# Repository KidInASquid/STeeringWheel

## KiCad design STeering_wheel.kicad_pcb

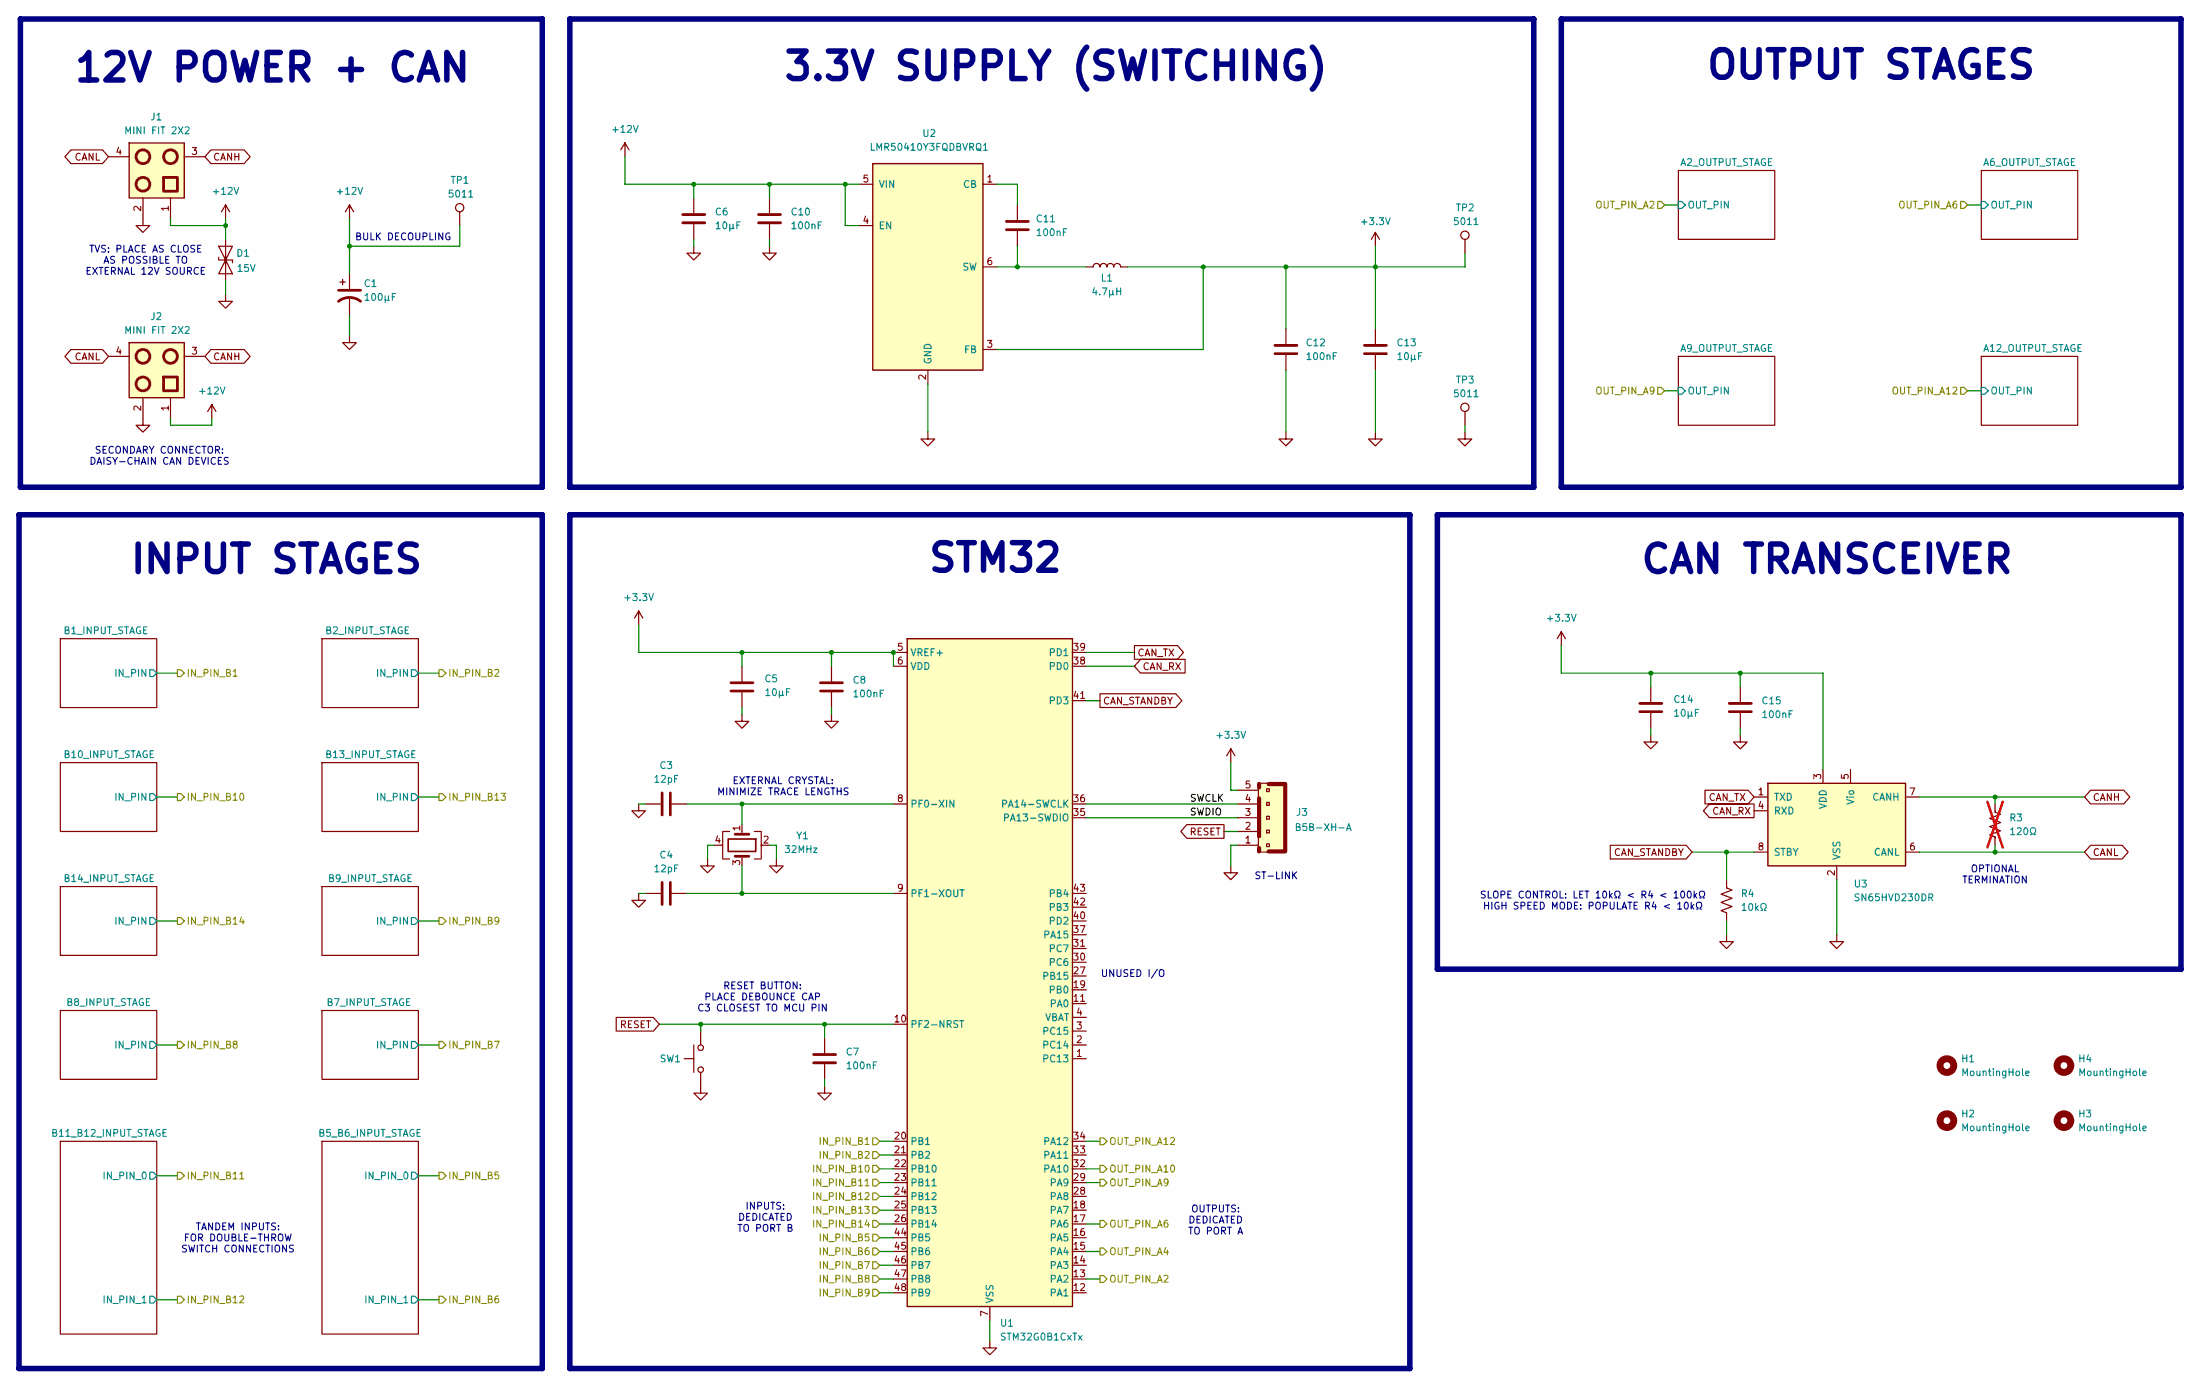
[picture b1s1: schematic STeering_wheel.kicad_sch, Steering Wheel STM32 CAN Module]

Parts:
C1: 100μF; CP_Radial_D5.0mm_P2.00mm; DigiKey Part Number P10369CT-ND
C3, C4: 12pF; C_0603_1608Metric; DigiKey Part Number 4713-CHV0805N250120FCT-ND
C5, C6, C13, C14: 10µF; C_0805_2012Metric; DigiKey Part Number 1276-1096-1-ND
C7, C8, C10, C11, C12, C15: 100nF; C_0805_2012Metric; DigiKey Part Number 1276-2442-1-ND
D1: AQHV15-01LTG-C; D_SOD-523; DigiKey Part Number AQHV15-01LTG-CCT-ND
H1, H2, H3, H4: MountingHole; MountingHole_3.2mm_M3_isolated_clearance
J1, J2: MINI FIT 2X2; Molex_Mini-Fit_Jr_5566-04A_2x02_P4.20mm_Vertical; DigiKey Part Number WM13112-ND
J3: B5B-XH-A; JST_XH_B5B-XH-A_1x05_P2.50mm_Vertical; DigiKey Part Number 455-B5B-XH-A-ND
L1: 4.7µH; L_1008_2520Metric; DigiKey Part Number 3526-WIP252010S-4R7MLDGCT-ND
R3: 120Ω; R_0805_2012Metric; DigiKey Part Number 2019-RK73H2ATTD1200FCT-ND; not fitted
R4: 10kΩ; R_0805_2012Metric; DigiKey Part Number 2019-RK73B2ATTD103JCT-ND
SW1: PTS636 SL50 SMTR LFS; SW_Tactile_SPST_NO_Straight_CK_PTS636Sx25SMTRLFS; DigiKey Part Number CKN12313-1-ND
TP1, TP2, TP3: 5011; keystone_5011_testpoint; DigiKey Part Number 36-5011-ND
U1: STM32G0B1CxTx; LQFP-48_7x7mm_P0.5mm; DigiKey Part Number 497-STM32G0B1KCT6-ND
U2: LMR50410Y3FQDBVRQ1; SOT-23-6; DigiKey Part Number 296-LMR50410Y3FQDBVRQ1CT-ND
U3: SN65HVD230DR; SOIC-8_3.9x4.9mm_P1.27mm_with_via_in_pads; DigiKey Part Number 296-11654-1-ND
Y1: 32MHz; XTAL_ECS-320-12-33B-7KM-TR; DigiKey Part Number 50-ECS-320-12-33B-7KM-CT-ND

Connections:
+3.3V: C5.1, C8.1, C12.1, C13.1, C14.1, C15.1, J3.5, L1.2, TP2.1, U1.5 (VREF+), U1.6 (VDD), U2.3 (FB), U3.3 (VDD); also elsewhere on the board
+12V: C1.1, C6.1, C10.1, D1.1 (A1), J1.1, J2.1, TP1.1, U2.4 (EN), U2.5 (VIN); also elsewhere on the board
/IN_PIN_B1: U1.20 (PB1); also elsewhere on the board
/IN_PIN_B2: U1.21 (PB2); also elsewhere on the board
/IN_PIN_B5: U1.44 (PB5); also elsewhere on the board
/IN_PIN_B6: U1.45 (PB6); also elsewhere on the board
/IN_PIN_B7: U1.46 (PB7); also elsewhere on the board
/IN_PIN_B8: U1.47 (PB8); also elsewhere on the board
/IN_PIN_B9: U1.48 (PB9); also elsewhere on the board
/IN_PIN_B10: U1.22 (PB10); also elsewhere on the board
/IN_PIN_B11: U1.23 (PB11); also elsewhere on the board
/IN_PIN_B12: U1.24 (PB12); also elsewhere on the board
/IN_PIN_B13: U1.25 (PB13); also elsewhere on the board
/IN_PIN_B14: U1.26 (PB14); also elsewhere on the board
/OUT_PIN_A2: U1.13 (PA2); also elsewhere on the board
/OUT_PIN_A4: U1.15 (PA4)
/OUT_PIN_A6: U1.17 (PA6); also elsewhere on the board
/OUT_PIN_A9: U1.29 (PA9); also elsewhere on the board
/OUT_PIN_A10: U1.32 (PA10)
/OUT_PIN_A12: U1.34 (PA12); also elsewhere on the board
/SWCLK: J3.4, U1.36 (PA14-SWCLK)
/SWDIO: J3.3, U1.35 (PA13-SWDIO)
CANH: J1.3, J2.3, R3.1, U3.7 (CANH)
CANL: J1.4, J2.4, R3.2, U3.6 (CANL)
CAN_RX: U1.38 (PD0), U3.4 (RXD)
CAN_STANDBY: R4.1, U1.41 (PD3), U3.8 (STBY)
CAN_TX: U1.39 (PD1), U3.1 (TXD)
GND: C1.2, C3.1, C4.1, C5.2, C6.2, C7.2, C8.2, C10.2, C12.2, C13.2, C14.2, C15.2, D1.2 (A2), J1.2, J2.2, J3.1, R4.2, SW1.1, TP3.1, U1.7 (VSS), U2.2 (GND), U3.2 (VSS), Y1.2, Y1.4; also elsewhere on the board
unnamed: C3.2, U1.8 (PF0-XIN), Y1.1
unnamed: C4.2, U1.9 (PF1-XOUT), Y1.3
unnamed: C11.1, U2.1 (CB)
unnamed: C11.2, L1.1, U2.6 (SW)
RESET: C7.1, J3.2, SW1.2, U1.10 (PF2-NRST)

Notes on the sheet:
3.3V SUPPLY (SWITCHING)
INPUTS: DEDICATED TO PORT B
12V POWER + CAN
EXTERNAL CRYSTAL: MINIMIZE TRACE LENGTHS
OUTPUT STAGES
OPTIONAL TERMINATION
CAN TRANSCEIVER
SECONDARY CONNECTOR: DAISY-CHAIN CAN DEVICES
OUTPUTS: DEDICATED TO PORT A
RESET BUTTON: PLACE DEBOUNCE CAP C3 CLOSEST TO MCU PIN
TVS: PLACE AS CLOSE AS POSSIBLE TO EXTERNAL 12V SOURCE
UNUSED I/O
STM32
SLOPE CONTROL: LET 10kΩ < R4 < 100kΩ HIGH SPEED MODE: POPULATE R4 < 10kΩ
BULK DECOUPLING
ST-LINK
TANDEM INPUTS: FOR DOUBLE-THROW SWITCH CONNECTIONS
INPUT STAGES

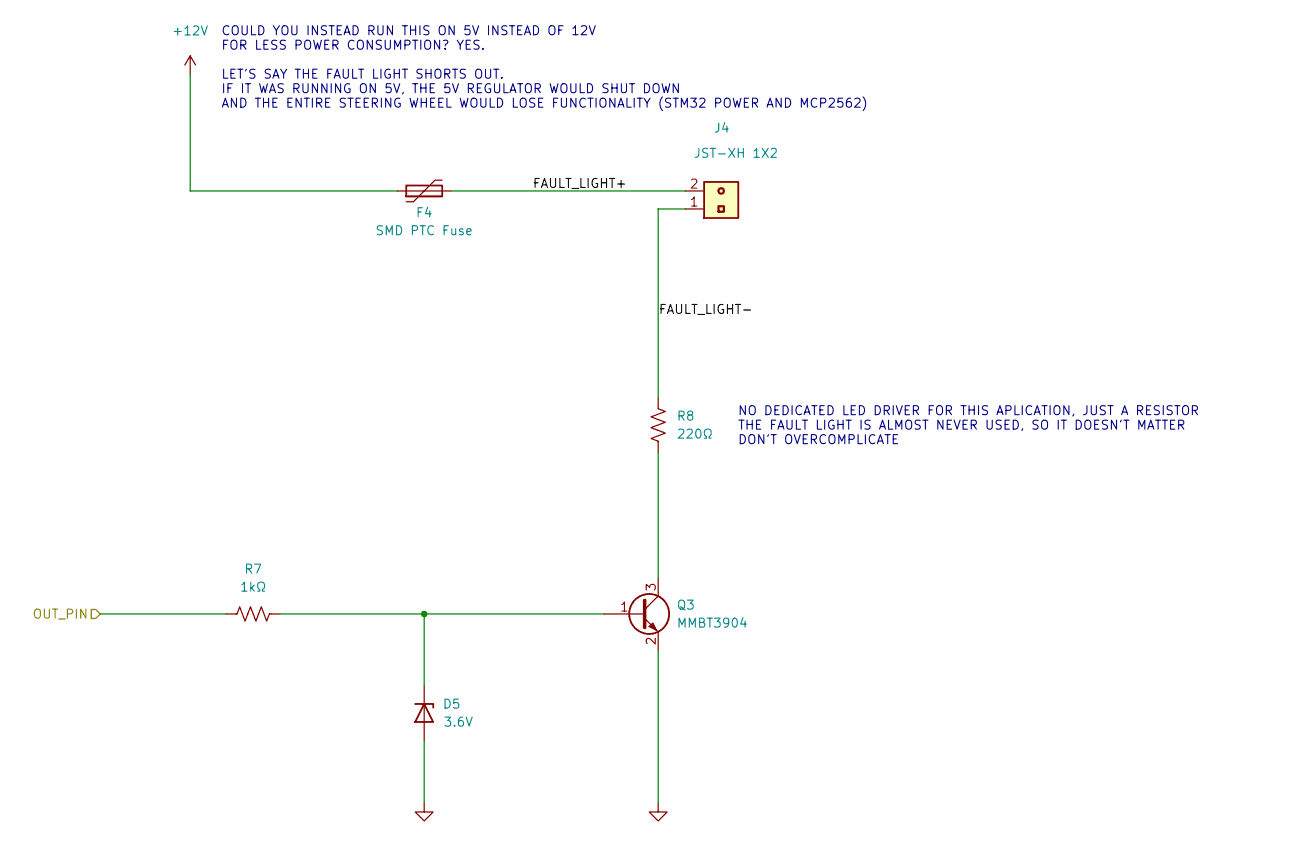
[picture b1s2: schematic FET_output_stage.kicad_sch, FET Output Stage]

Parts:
D5: ESD321DYAR; D_SOD-523; DigiKey Part Number 296-ESD321DYARCT-ND
F4: PRG21BC2R2MM1RA; Fuse_0805_2012Metric; DigiKey Part Number 490-8512-1-ND
J4: JST-XH 1X2; JST_XH_B2B-XH-AM_1x02_P2.50mm_Vertical; DigiKey Part Number WM14662-ND
Q3: MMBT3904; SOT-23; DigiKey Part Number 4530-MMBT3904CT-ND
R7: 1kΩ; R_0805_2012Metric; DigiKey Part Number 2019-RK73B2ATTD102JCT-ND
R8: 220Ω; R_0805_2012Metric

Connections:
+12V: F4.1; also elsewhere on the board
/A2_OUTPUT_STAGE/FAULT_LIGHT+: F4.2, J4.2
/A2_OUTPUT_STAGE/FAULT_LIGHT-: J4.1, R8.2
/OUT_PIN_A2: R7.1; also elsewhere on the board
GND: D5.2 (A), Q3.2 (E); also elsewhere on the board
unnamed: D5.1 (K), Q3.1 (B), R7.2
unnamed: Q3.3 (C), R8.1

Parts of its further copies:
D2, D3, D4: ESD321DYAR; D_SOD-523; DigiKey Part Number 296-ESD321DYARCT-ND
F1, F2, F3: PRG21BC2R2MM1RA; Fuse_0805_2012Metric; DigiKey Part Number 490-8512-1-ND
J5, J6, J7: JST-XH 1X2; JST_XH_B2B-XH-AM_1x02_P2.50mm_Vertical; DigiKey Part Number WM14662-ND
Q1, Q2, Q4: MMBT3904; SOT-23; DigiKey Part Number 4530-MMBT3904CT-ND
R1, R5, R9: 1kΩ; R_0805_2012Metric; DigiKey Part Number 2019-RK73B2ATTD102JCT-ND
R2, R6, R10: 220Ω; R_0805_2012Metric

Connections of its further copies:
+12V: F1.1, F2.1, F3.1; also elsewhere on the board
/A6_OUTPUT_STAGE/FAULT_LIGHT+: F1.2, J5.2
/A6_OUTPUT_STAGE/FAULT_LIGHT-: J5.1, R2.2
/A9_OUTPUT_STAGE/FAULT_LIGHT+: F2.2, J6.2
/A9_OUTPUT_STAGE/FAULT_LIGHT-: J6.1, R6.2
/A12_OUTPUT_STAGE/FAULT_LIGHT+: F3.2, J7.2
/A12_OUTPUT_STAGE/FAULT_LIGHT-: J7.1, R10.2
/OUT_PIN_A6: R1.1; also elsewhere on the board
/OUT_PIN_A9: R5.1; also elsewhere on the board
/OUT_PIN_A12: R9.1; also elsewhere on the board
GND: D2.2 (A), D3.2 (A), D4.2 (A), Q1.2 (E), Q2.2 (E), Q4.2 (E); also elsewhere on the board
unnamed: D2.1 (K), Q1.1 (B), R1.2
unnamed: D3.1 (K), Q2.1 (B), R5.2
unnamed: D4.1 (K), Q4.1 (B), R9.2
unnamed: Q1.3 (C), R2.1
unnamed: Q2.3 (C), R6.1
unnamed: Q4.3 (C), R10.1

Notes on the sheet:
NO DEDICATED LED DRIVER FOR THIS APLICATION, JUST A RESISTOR THE FAULT LIGHT IS ALMOST NEVER USED, SO IT DOESN'T MATTER DON'T OVERCOMPLICATE
COULD YOU INSTEAD RUN THIS ON 5V INSTEAD OF 12V FOR LESS POWER CONSUMPTION? YES. LET'S SAY THE FAULT LIGHT SHORTS OUT. IF IT WAS RUNNING ON 5V, THE 5V REGULATOR WOULD SHUT DOWN AND THE ENTIRE STEERING WHEEL WOULD LOSE FUNCTIONALITY (STM32 POWER AND MCP2562)

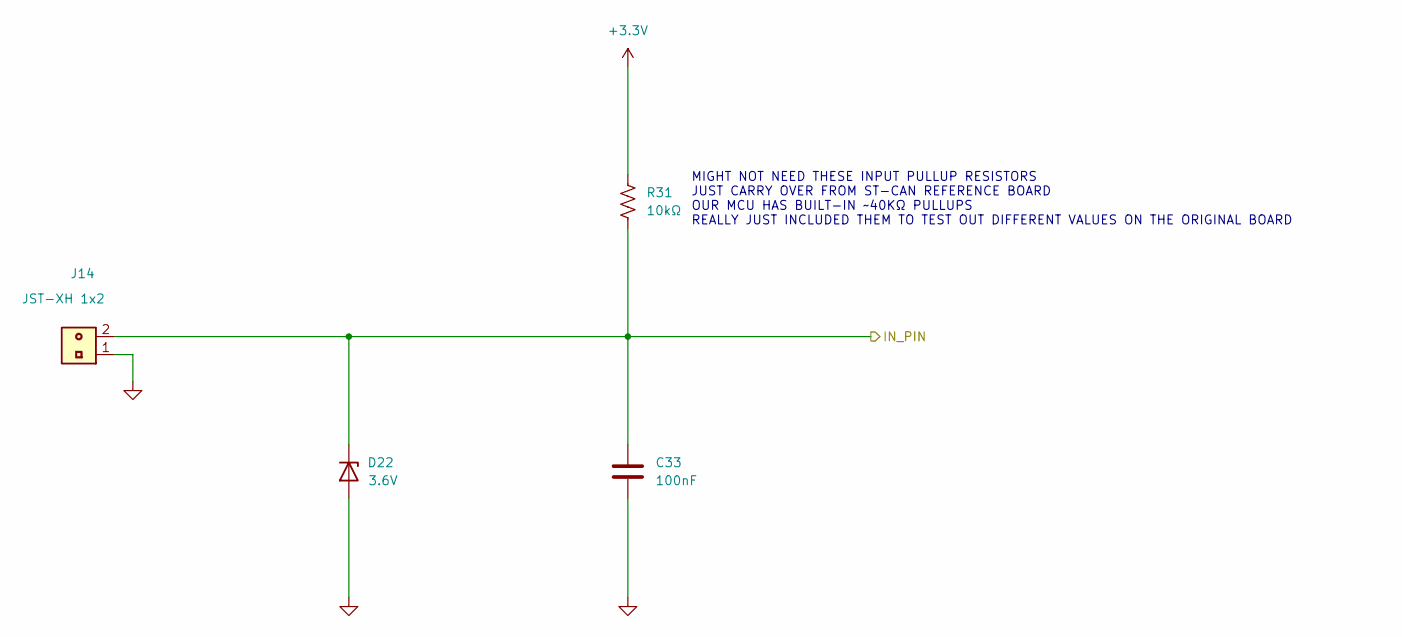
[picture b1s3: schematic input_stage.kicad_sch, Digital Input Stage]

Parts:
C33: 100nF; C_0805_2012Metric; DigiKey Part Number 1276-2442-1-ND
D22: ESD321DYAR; D_SOD-523; DigiKey Part Number 296-ESD321DYARCT-ND
J14: JST-XH 1x2; JST_XH_B2B-XH-AM_1x02_P2.50mm_Vertical; DigiKey Part Number WM14662-ND
R31: 10kΩ; R_0805_2012Metric; DigiKey Part Number 2019-RK73B2ATTD103JCT-ND

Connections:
+3.3V: R31.1; also elsewhere on the board
/IN_PIN_B10: C33.1, D22.1 (K), J14.2, R31.2; also elsewhere on the board
GND: C33.2, D22.2 (A), J14.1; also elsewhere on the board

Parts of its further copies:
C31, C32, C34, C35, C36, C37, C38: 100nF; C_0805_2012Metric; DigiKey Part Number 1276-2442-1-ND
D20, D21, D23, D24, D25, D26, D27: ESD321DYAR; D_SOD-523; DigiKey Part Number 296-ESD321DYARCT-ND
J12, J13, J15, J16, J17, J18, J19: JST-XH 1x2; JST_XH_B2B-XH-AM_1x02_P2.50mm_Vertical; DigiKey Part Number WM14662-ND
R24, R25, R26, R27, R28, R29, R30: 10kΩ; R_0805_2012Metric; DigiKey Part Number 2019-RK73B2ATTD103JCT-ND

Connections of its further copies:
+3.3V: R24.1, R25.1, R26.1, R27.1, R28.1, R29.1, R30.1; also elsewhere on the board
/IN_PIN_B1: C32.1, D21.1 (K), J13.2, R29.2; also elsewhere on the board
/IN_PIN_B2: C31.1, D20.1 (K), J12.2, R30.2; also elsewhere on the board
/IN_PIN_B7: C38.1, D27.1 (K), J19.2, R24.2; also elsewhere on the board
/IN_PIN_B8: C37.1, D26.1 (K), J18.2, R25.2; also elsewhere on the board
/IN_PIN_B9: C36.1, D25.1 (K), J17.2, R26.2; also elsewhere on the board
/IN_PIN_B13: C34.1, D23.1 (K), J15.2, R28.2; also elsewhere on the board
/IN_PIN_B14: C35.1, D24.1 (K), J16.2, R27.2; also elsewhere on the board
GND: C31.2, C32.2, C34.2, C35.2, C36.2, C37.2, C38.2, D20.2 (A), D21.2 (A), D23.2 (A), D24.2 (A), D25.2 (A), D26.2 (A), D27.2 (A), J12.1, J13.1, J15.1, J16.1, J17.1, J18.1, J19.1; also elsewhere on the board

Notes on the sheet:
MIGHT NOT NEED THESE INPUT PULLUP RESISTORS JUST CARRY OVER FROM ST-CAN REFERENCE BOARD OUR MCU HAS BUILT-IN ~40KΩ PULLUPS REALLY JUST INCLUDED THEM TO TEST OUT DIFFERENT VALUES ON THE ORIGINAL BOARD

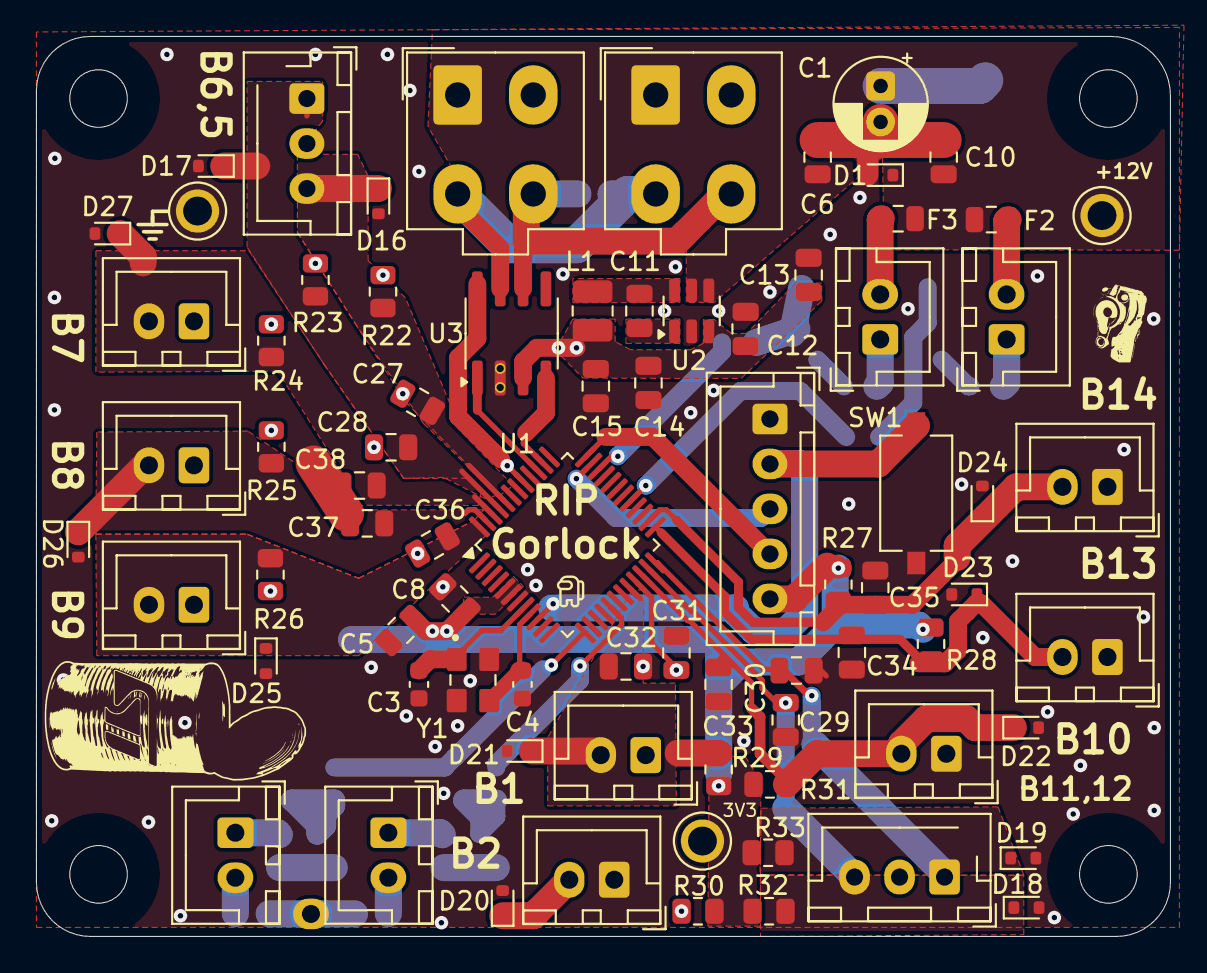
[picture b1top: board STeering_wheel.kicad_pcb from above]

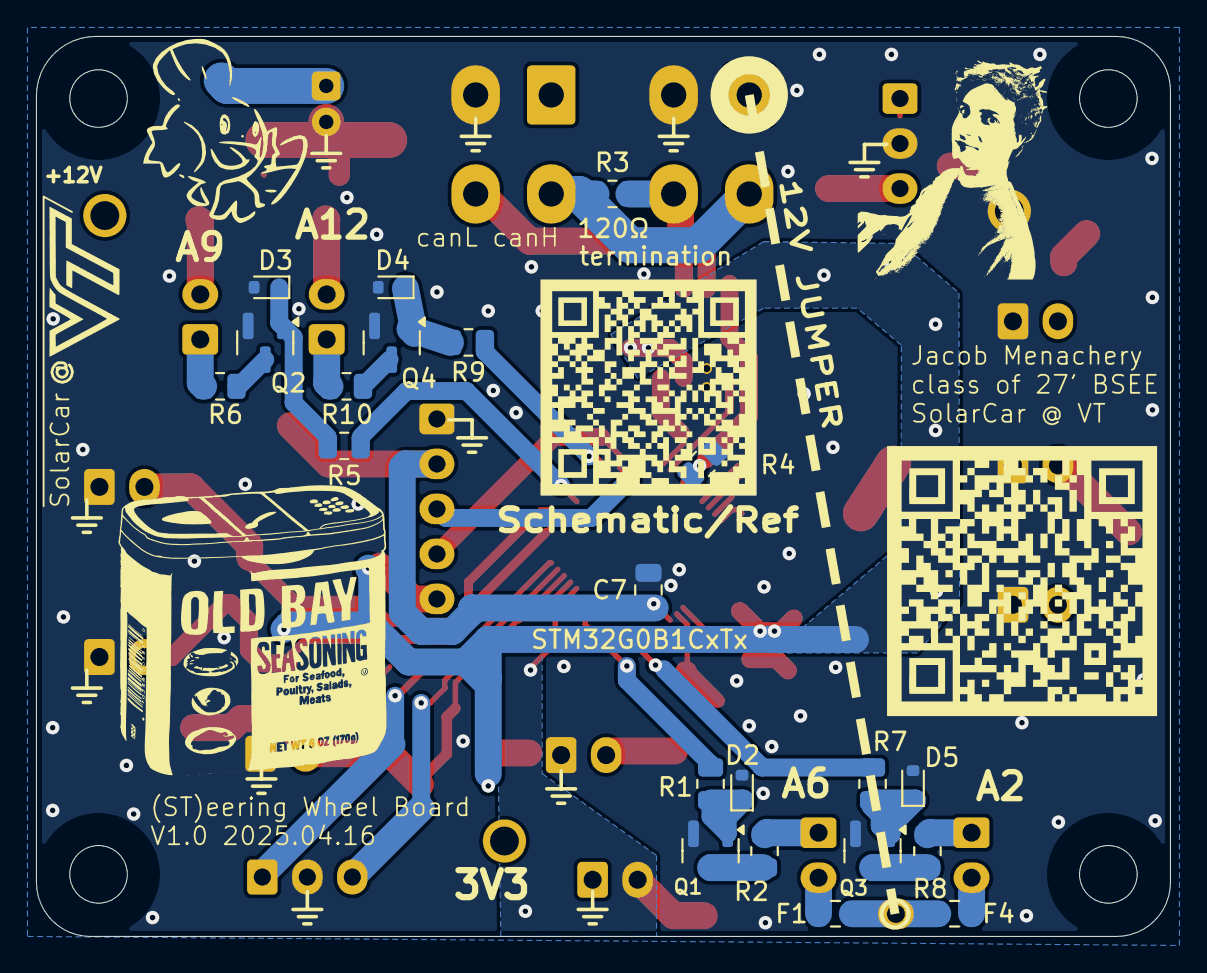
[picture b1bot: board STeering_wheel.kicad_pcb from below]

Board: 2 copper layers, 63.0 x 50.0 mm, 102 parts (21 on the bottom side), 47 nets.

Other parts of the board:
C27, C28, C29, C30: 100nF; C_0805_2012Metric
D16, D17, D18, D19: ESD321DYAR; D_SOD-523
J10, J11: JST-XH1X3; JST_XH_B3B-XH-AM_1x03_P2.50mm_Vertical
R22, R23, R32, R33: 10kΩ; R_0805_2012Metric

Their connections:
+3.3V: R22.1, R23.1, R32.1, R33.1; also elsewhere on the board
/IN_PIN_B5: C27.1, D16.1 (K), J10.3, R22.2; also elsewhere on the board
/IN_PIN_B6: C28.1, D17.1 (K), J10.1, R23.2; also elsewhere on the board
/IN_PIN_B11: C29.1, D18.1 (K), J11.3, R32.2; also elsewhere on the board
/IN_PIN_B12: C30.1, D19.1 (K), J11.1, R33.2; also elsewhere on the board
GND: C27.2, C28.2, C29.2, C30.2, D16.2 (A), D17.2 (A), D18.2 (A), D19.2 (A), J10.2, J11.2; also elsewhere on the board

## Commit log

2025-04-29 updated Files
